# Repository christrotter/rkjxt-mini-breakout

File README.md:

# rkjxt-mini-breakout
Mini-breakout for the RKJXT1F42001 multi-function switch.

# Releases
* v0.1: https://github.com/christrotter/rkjxt-mini-breakout/releases/tag/v0.1

# Project goals
First time trying diy pcb, so 'learn how to pcb' was a major goal.

The goal of this pcb is:
* minimal footprint
* M3 mounting tabs (_cuz that's what I have on hand_)
* 2.54mm pin spacing on breakout; ability to use 6-pin JST-XH 2.54mm headers (_cuz that's what I have on hand_)
* SMD diode for row (_cuz that's what I have on hand_)
* col2row, cols on A/B/C/D, row on COM

I needed a better 5-way switch for the mk18 project.  In the past I picked up some RKJXT1F42001 encoders/5-ways on the recommendation of QMK folks, but they needed a pcb to actually be used.
They have almost zero slop/play and fit in the same footprint as the other 5-way switches, plus have an EC11 encoder built-in, and a 'joystick' effect.

In theory I can keep the same used space and so the same mounting location, i.e. right above the trackball.

# Pictures

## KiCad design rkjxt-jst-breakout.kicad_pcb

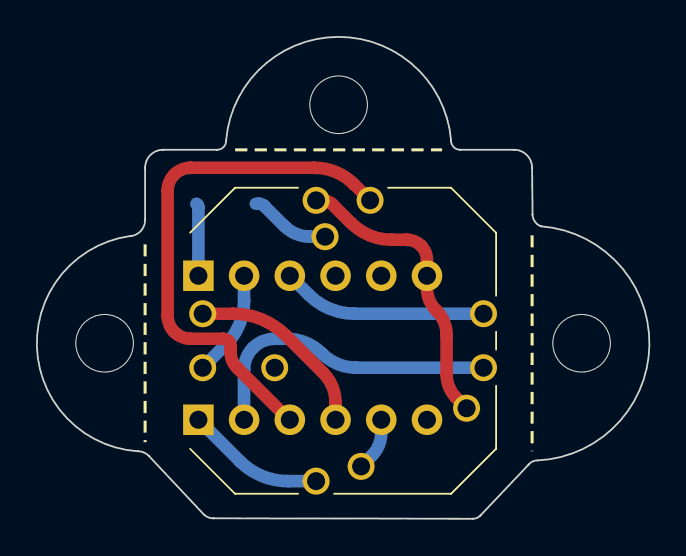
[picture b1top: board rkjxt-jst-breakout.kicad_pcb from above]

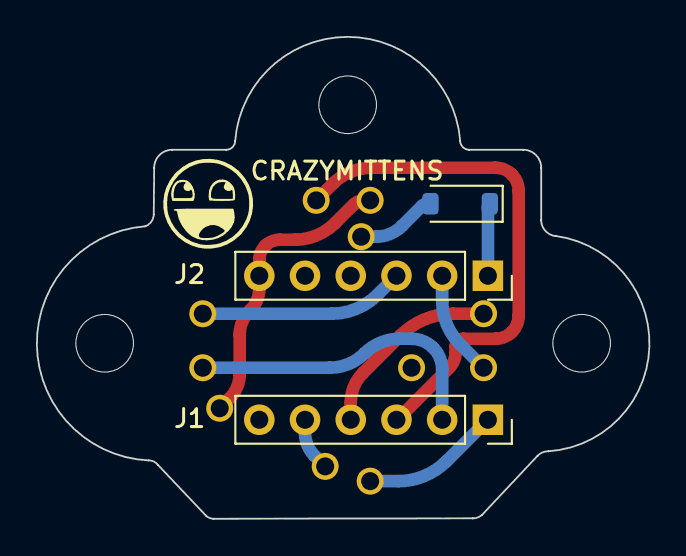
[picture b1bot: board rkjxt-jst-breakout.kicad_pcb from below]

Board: 2 copper layers, 34.0 x 26.8 mm, 7 parts (3 on the bottom side), 10 nets.

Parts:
D1: 1N4148W; D_SOD-123
H1, H2, H3: MountingHole_3.2mm_M3
JST1, JST2: Conn_01x06_Socket; PinSocket_1x06_P2.54mm_Vertical
S1: RKJXT1F42001

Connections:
COM: D1.2 (A), S1.7 (COM)
Gnd: JST2.6, S1.3 (GND_TERMINAL), S1.8 (ENCODER_COM)
col1: JST1.1, S1.1 (A)
col2: JST1.2, S1.4 (B)
col3: JST1.3, S1.6 (C)
col4: JST1.4, S1.9 (D_1)
col5: JST1.5, S1.2 (PUSH)
encA: JST2.2, S1.10 (ENCODER_A)
encB: JST2.3, S1.5 (ENCODER_B)
row1: D1.1 (K), JST2.1

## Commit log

2023-10-25 first commit of files
2023-10-25 updating readme
2023-10-25 fixing some issues, adding images
2023-10-25 deleting stuff
2023-10-25 adding kicad gitignore
2023-10-25 updating gitignore and removing the zip
